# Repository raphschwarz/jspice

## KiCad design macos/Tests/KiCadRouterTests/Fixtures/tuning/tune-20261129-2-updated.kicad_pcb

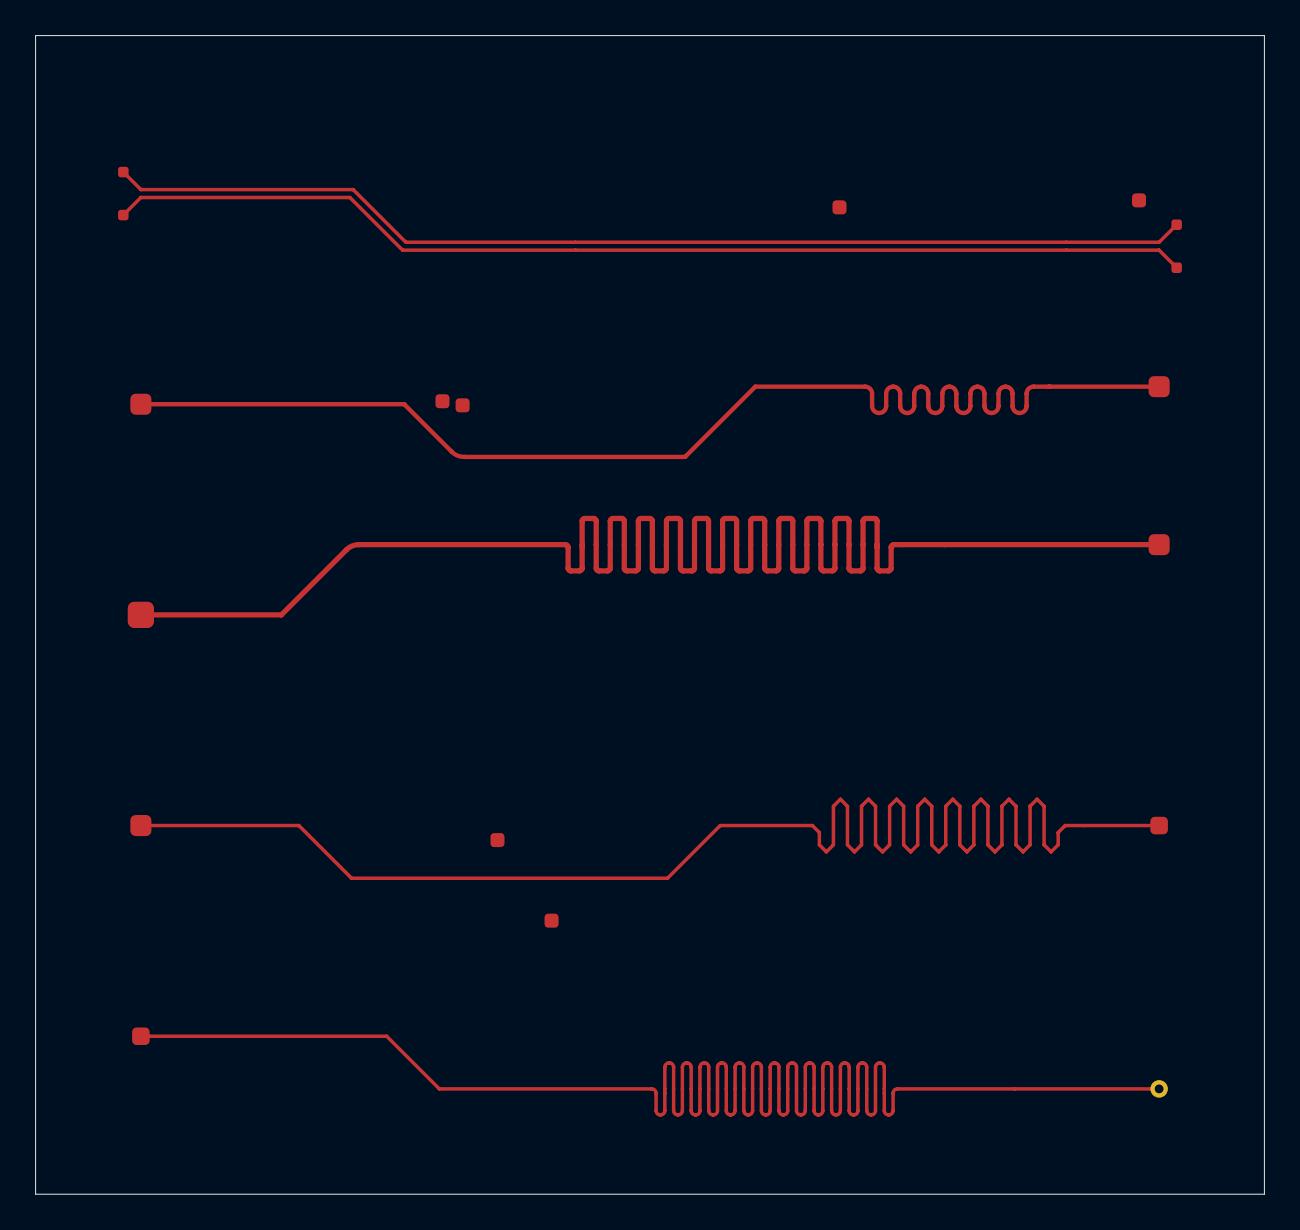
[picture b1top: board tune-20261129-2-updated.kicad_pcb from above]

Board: 2 copper layers, 70.0 x 66.0 mm, 18 parts (0 on the bottom side), 6 nets.

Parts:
P1, P5, P9, P13, P27, P31, P35, P39, P49, P53, P57, P61, P69, P73, P82, P86, P90, P94: Pad

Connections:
D1_N: P9.1, P13.1
D1_P: P1.1, P5.1
S2: P35.1, P39.1
S3: P57.1, P61.1
S4: P69.1, P73.1
S5: P90.1, P94.1

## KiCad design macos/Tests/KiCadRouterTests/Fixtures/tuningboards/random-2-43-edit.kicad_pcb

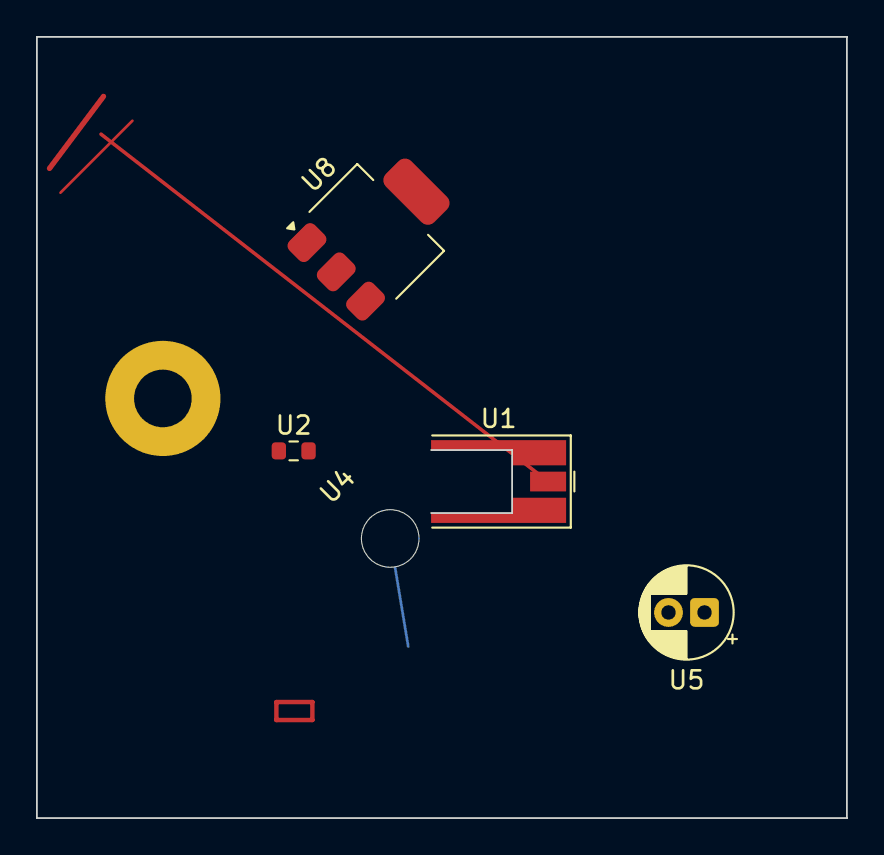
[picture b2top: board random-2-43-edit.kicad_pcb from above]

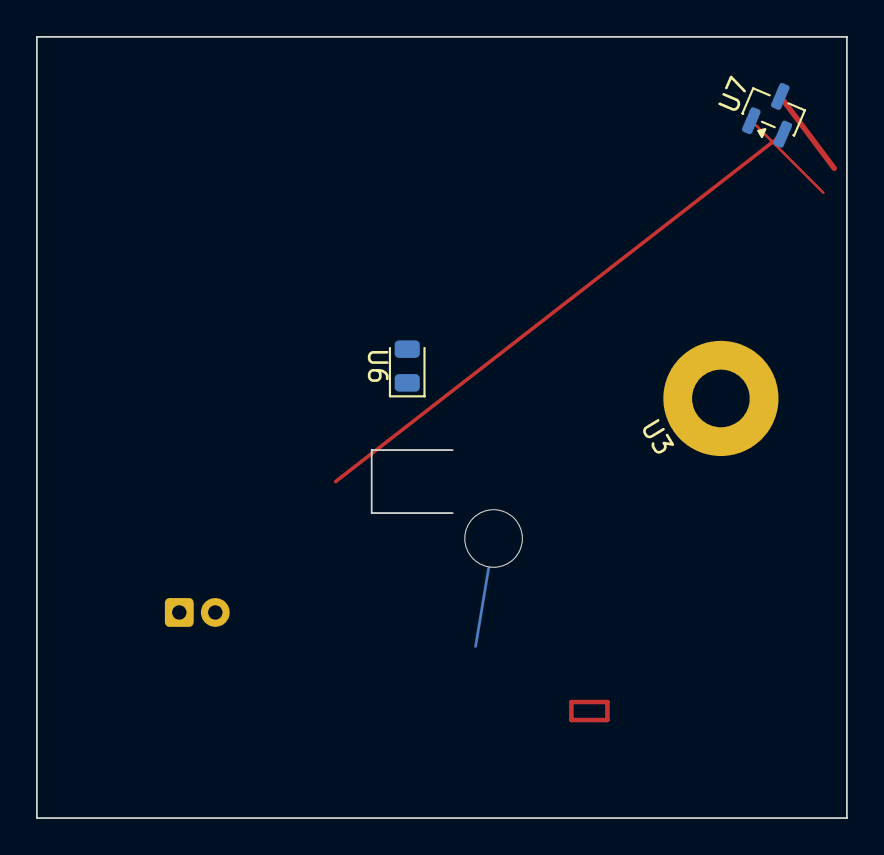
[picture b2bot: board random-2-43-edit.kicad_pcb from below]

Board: 4 copper layers, 45.0 x 43.4 mm, 8 parts (3 on the bottom side), 3 nets.

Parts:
U1: MMCX_Molex_73415-0961_Horizontal_0.8mm-PCB
U2: R_0603_1608Metric
U3: MountingHole_3.2mm_M3_Pad
U4: MountingHole_3.2mm_M3
U5: CP_Radial_D5.0mm_P2.00mm
U6: LED_0805_2012Metric
U7: SOT-23
U8: SOT-223-3_TabPin2

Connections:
D12: U6.1, U7.2
N1: U3.1, U6.2
N3: U2.2, U7.3, U8.3

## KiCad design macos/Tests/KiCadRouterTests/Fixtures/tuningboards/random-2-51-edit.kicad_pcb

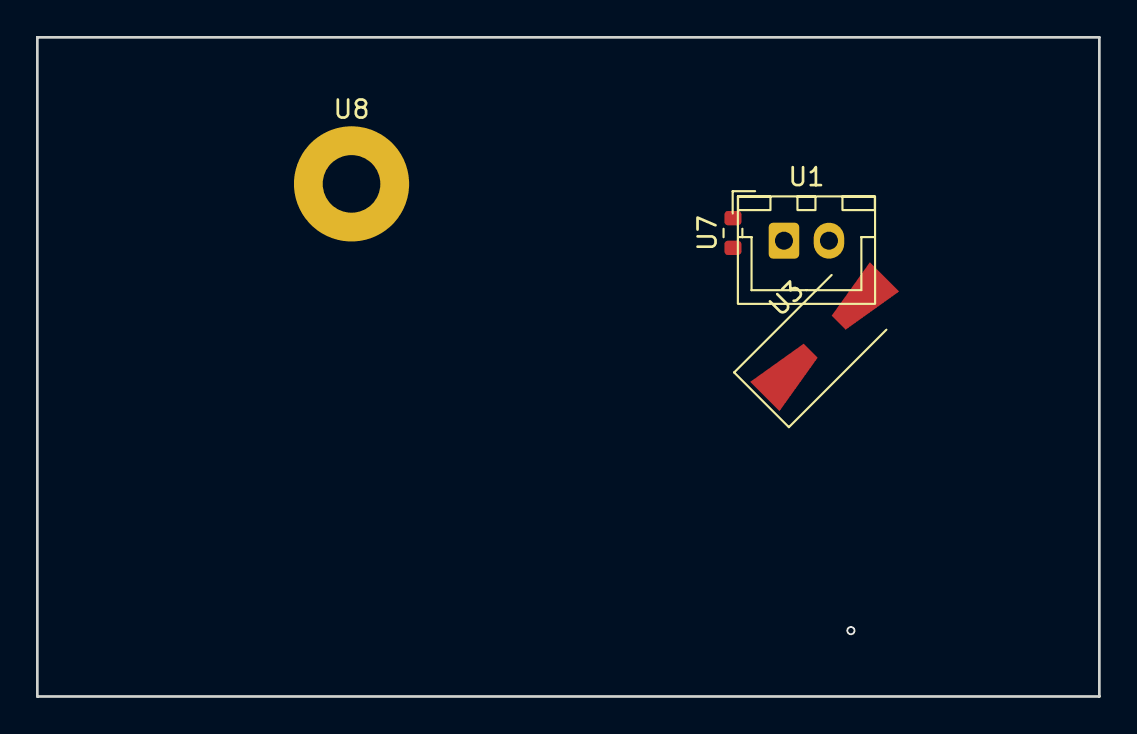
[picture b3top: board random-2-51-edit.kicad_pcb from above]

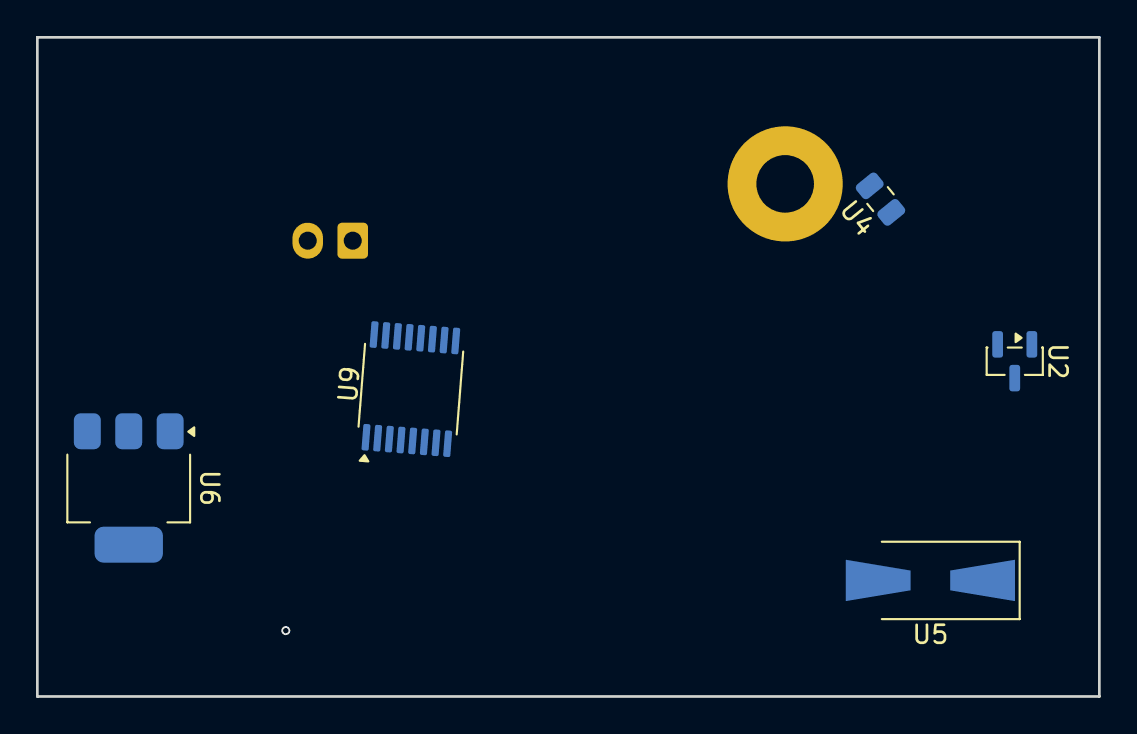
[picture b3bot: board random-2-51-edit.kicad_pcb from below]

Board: 4 copper layers, 59.0 x 36.6 mm, 9 parts (5 on the bottom side), 6 nets.

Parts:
U1: JST_XH_B2B-XH-A_1x02_P2.50mm_Vertical
U2: SOT-23
U3, U5: D_SMA-SMB_Universal_Handsoldering
U4: C_0805_2012Metric
U6: SOT-223-3_TabPin2
U7: R_0603_1608Metric
U8: MountingHole_3.2mm_M3_Pad
U9: TSSOP-16_4.4x5mm_P0.65mm

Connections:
GND: U7.1, U9.2, U9.7, U9.8
N2: U1.2, U9.1
PWR_5V: U9.10, U9.11
SIG1: U6.1, U6.2, U7.2, U9.6
SIG2: U2.2, U6.2
VCC: U2.3, U3.1, U3.2, U9.15
